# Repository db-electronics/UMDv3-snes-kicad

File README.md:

# UMDv3 Super Nintendo Cartridge adapter
The [Universal Mega Dumper v3](https://github.com/db-electronics/UMDv3) project is an open-source solution for cartridge dumping and writing. 

This PCB interfaces a Super Nintendo cartridge to the UMDv3. The [UMDv3 Main PCB](https://github.com/db-electronics/UMDv3-kicad) detects which cartridge adapter is currently connected by reading an ID byte on the I2C bus provided by an MCP23008. The Super Nintendo ID is 0x03.

# Project
Please refer to the [UMDv3 Firmware Project Repository](https://github.com/db-electronics/UMDv3) for UMDv3 documentation and instructions; this is the project's central repository and where the wiki is hosted.

# Dependencies
## Parts Libraries
All components in this PCB depend on [my KiCad libraries](https://github.com/db-electronics/kicadlib) which are available here on github. I don't use any pre-existing libraries - *fight me*.

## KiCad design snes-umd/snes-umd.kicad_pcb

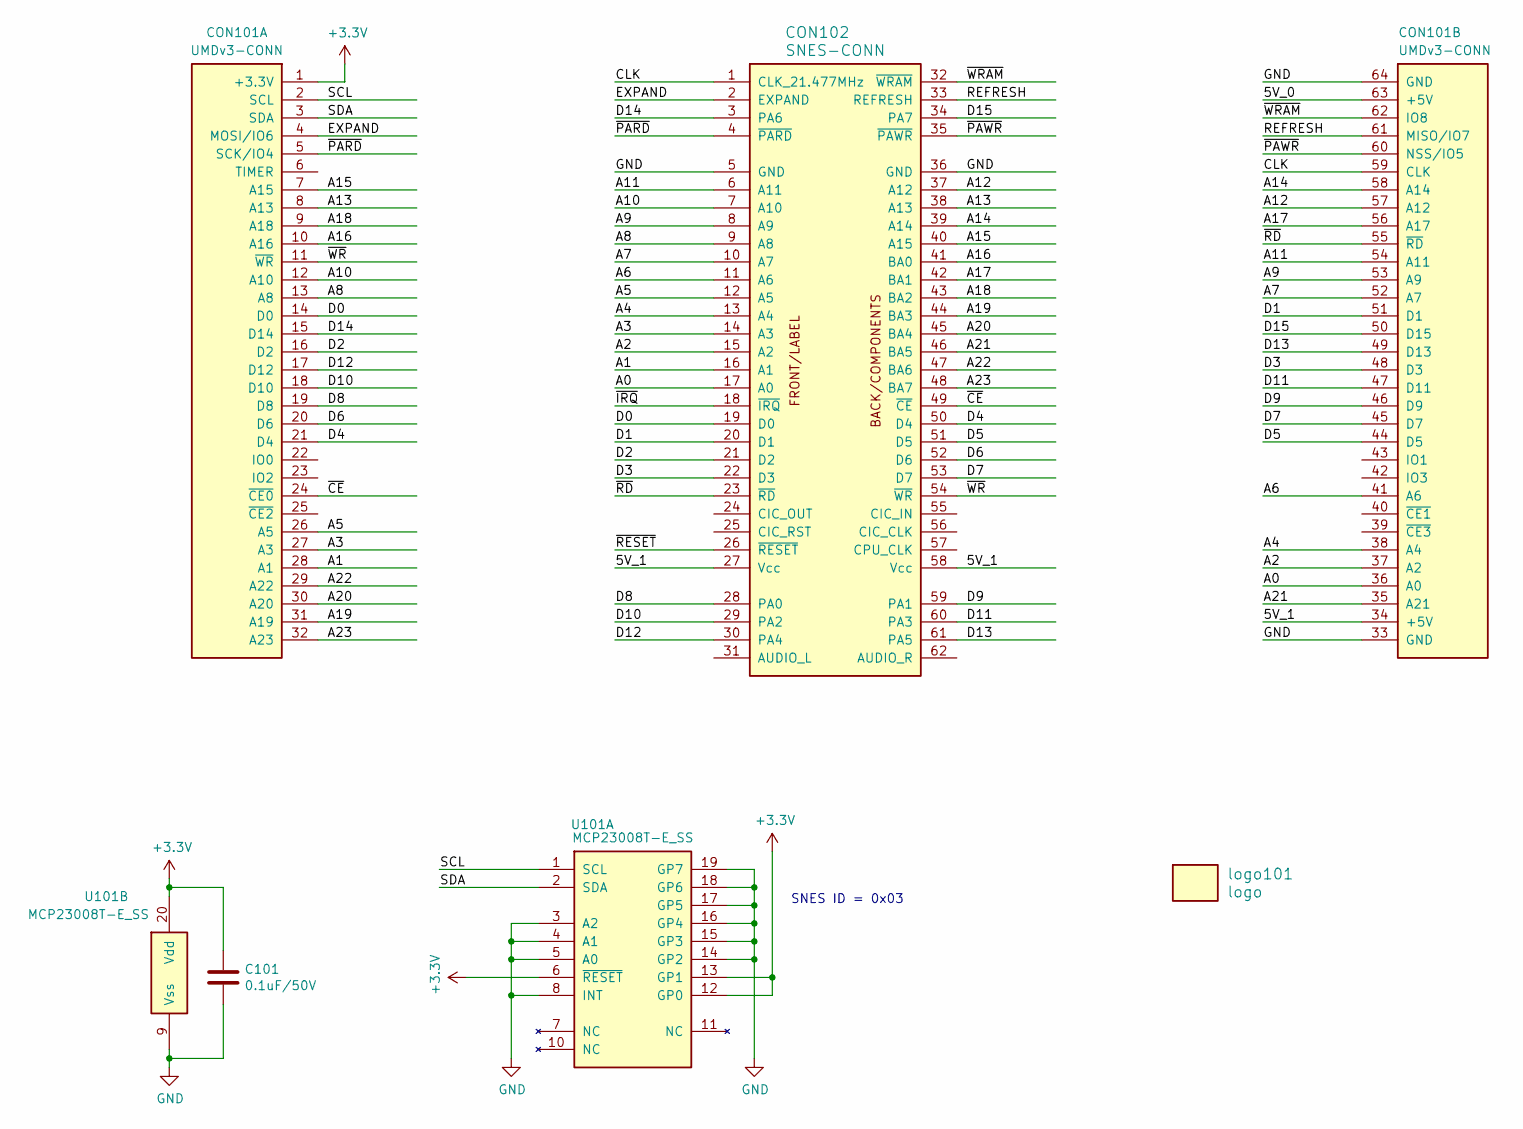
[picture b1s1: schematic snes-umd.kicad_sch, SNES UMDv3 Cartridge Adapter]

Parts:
C101: 0.1uF/50V; 0603; Digikey 478-5052-1-ND
CON101: UMDv3-CONN; UMDv3-CONN-DIP64; Digikey SAM1211-32-ND
CON102: SNES-CONN; SNES-CONN-EXP
U101: MCP23008T-E_SS; SSOP-20; Digikey MCP23008T-E/SSCT-ND
logo101: logo; db-logo_7.5mm

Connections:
+3V3: C101.1, CON101.1 (+3.3V), U101.6 (~RESET), U101.12 (GP0), U101.13 (GP1), U101.20 (Vdd)
/5V_0: CON101.63 (+5V)
/5V_1: CON101.34 (+5V), CON102.27 (Vcc), CON102.58 (Vcc)
/A0: CON101.36 (A0), CON102.17 (A0)
/A1: CON101.28 (A1), CON102.16 (A1)
/A2: CON101.37 (A2), CON102.15 (A2)
/A3: CON101.27 (A3), CON102.14 (A3)
/A4: CON101.38 (A4), CON102.13 (A4)
/A5: CON101.26 (A5), CON102.12 (A5)
/A6: CON101.41 (A6), CON102.11 (A6)
/A7: CON101.52 (A7), CON102.10 (A7)
/A8: CON101.13 (A8), CON102.9 (A8)
/A9: CON101.53 (A9), CON102.8 (A9)
/A10: CON101.12 (A10), CON102.7 (A10)
/A11: CON101.54 (A11), CON102.6 (A11)
/A12: CON101.57 (A12), CON102.37 (A12)
/A13: CON101.8 (A13), CON102.38 (A13)
/A14: CON101.58 (A14), CON102.39 (A14)
/A15: CON101.7 (A15), CON102.40 (A15)
/A16: CON101.10 (A16), CON102.41 (BA0)
/A17: CON101.56 (A17), CON102.42 (BA1)
/A18: CON101.9 (A18), CON102.43 (BA2)
/A19: CON101.31 (A19), CON102.44 (BA3)
/A20: CON101.30 (A20), CON102.45 (BA4)
/A21: CON101.35 (A21), CON102.46 (BA5)
/A22: CON101.29 (A22), CON102.47 (BA6)
/A23: CON101.32 (A23), CON102.48 (BA7)
/CLK: CON101.59 (CLK), CON102.1 (CLK_21.477MHz)
/D0: CON101.14 (D0), CON102.19 (D0)
/D1: CON101.51 (D1), CON102.20 (D1)
/D2: CON101.16 (D2), CON102.21 (D2)
/D3: CON101.48 (D3), CON102.22 (D3)
/D4: CON101.21 (D4), CON102.50 (D4)
/D5: CON101.44 (D5), CON102.51 (D5)
/D6: CON101.20 (D6), CON102.52 (D6)
/D7: CON101.45 (D7), CON102.53 (D7)
/D8: CON101.19 (D8), CON102.28 (PA0)
/D9: CON101.46 (D9), CON102.59 (PA1)
/D10: CON101.18 (D10), CON102.29 (PA2)
/D11: CON101.47 (D11), CON102.60 (PA3)
/D12: CON101.17 (D12), CON102.30 (PA4)
/D13: CON101.49 (D13), CON102.61 (PA5)
/D14: CON101.15 (D14), CON102.3 (PA6)
/D15: CON101.50 (D15), CON102.34 (PA7)
/EXPAND: CON101.4 (MOSI/IO6), CON102.2 (EXPAND)
/REFRESH: CON101.61 (MISO/IO7), CON102.33 (REFRESH)
/SCL: CON101.2 (SCL), U101.1 (SCL)
/SDA: CON101.3 (SDA), U101.2 (SDA)
/~CE: CON101.24 (~CE0), CON102.49 (~CE)
/~IRQ: CON102.18 (~IRQ)
/~PARD: CON101.5 (SCK/IO4), CON102.4 (~PARD)
/~PAWR: CON101.60 (NSS/IO5), CON102.35 (~PAWR)
/~RD: CON101.55 (~RD), CON102.23 (~RD)
/~RESET: CON102.26 (~RESET)
/~WRAM: CON101.62 (IO8), CON102.32 (~WRAM)
/~WR: CON101.11 (~WR), CON102.54 (~WR)
GND: C101.2, CON101.33 (GND), CON101.64 (GND), CON102.5 (GND), CON102.36 (GND), U101.3 (A2), U101.4 (A1), U101.5 (A0), U101.8 (INT), U101.9 (Vss), U101.14 (GP2), U101.15 (GP3), U101.16 (GP4), U101.17 (GP5), U101.18 (GP6), U101.19 (GP7)

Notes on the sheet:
SNES ID = 0x03

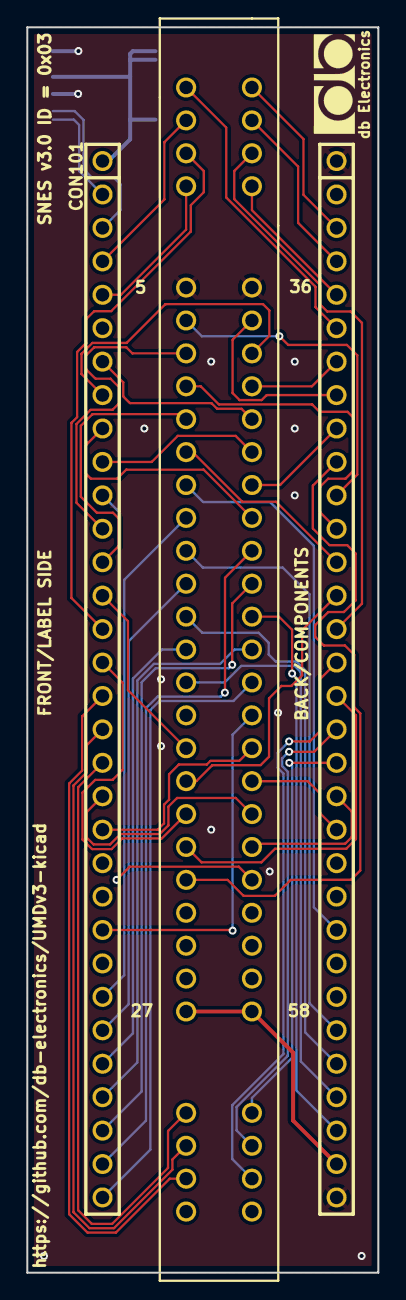
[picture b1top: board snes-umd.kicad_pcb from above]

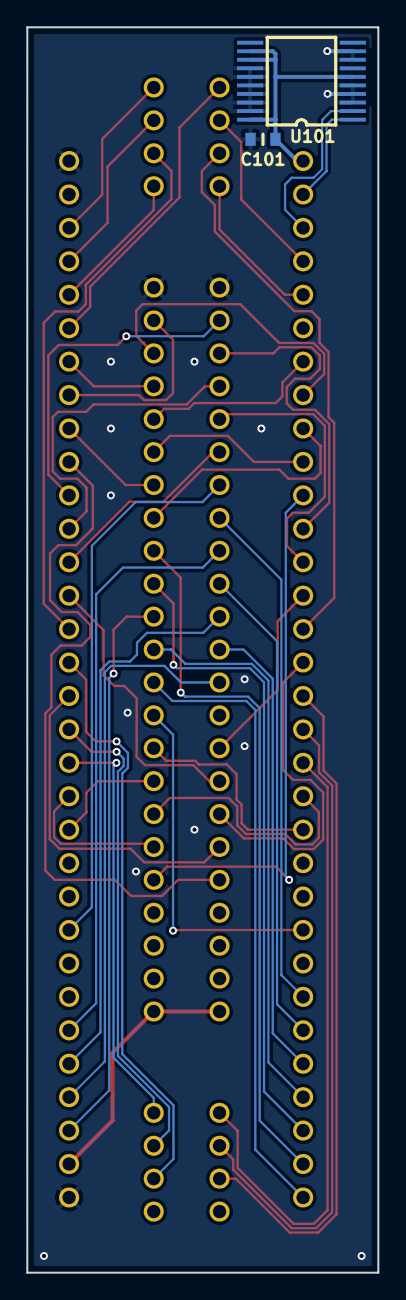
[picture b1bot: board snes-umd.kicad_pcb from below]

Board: 2 copper layers, 26.7 x 94.6 mm, 5 parts (2 on the bottom side), 54 nets.

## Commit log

2024-03-16 initial files commit
2024-03-17 board outline and sch mostly done
2024-03-17 layout almost complete
2024-03-17 version 3.0 files
2024-03-19 funding.yml and update readme

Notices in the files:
snes-umd/snes-umd.kicad_pcb:
Licensed under the CERN OHL v.1.2
